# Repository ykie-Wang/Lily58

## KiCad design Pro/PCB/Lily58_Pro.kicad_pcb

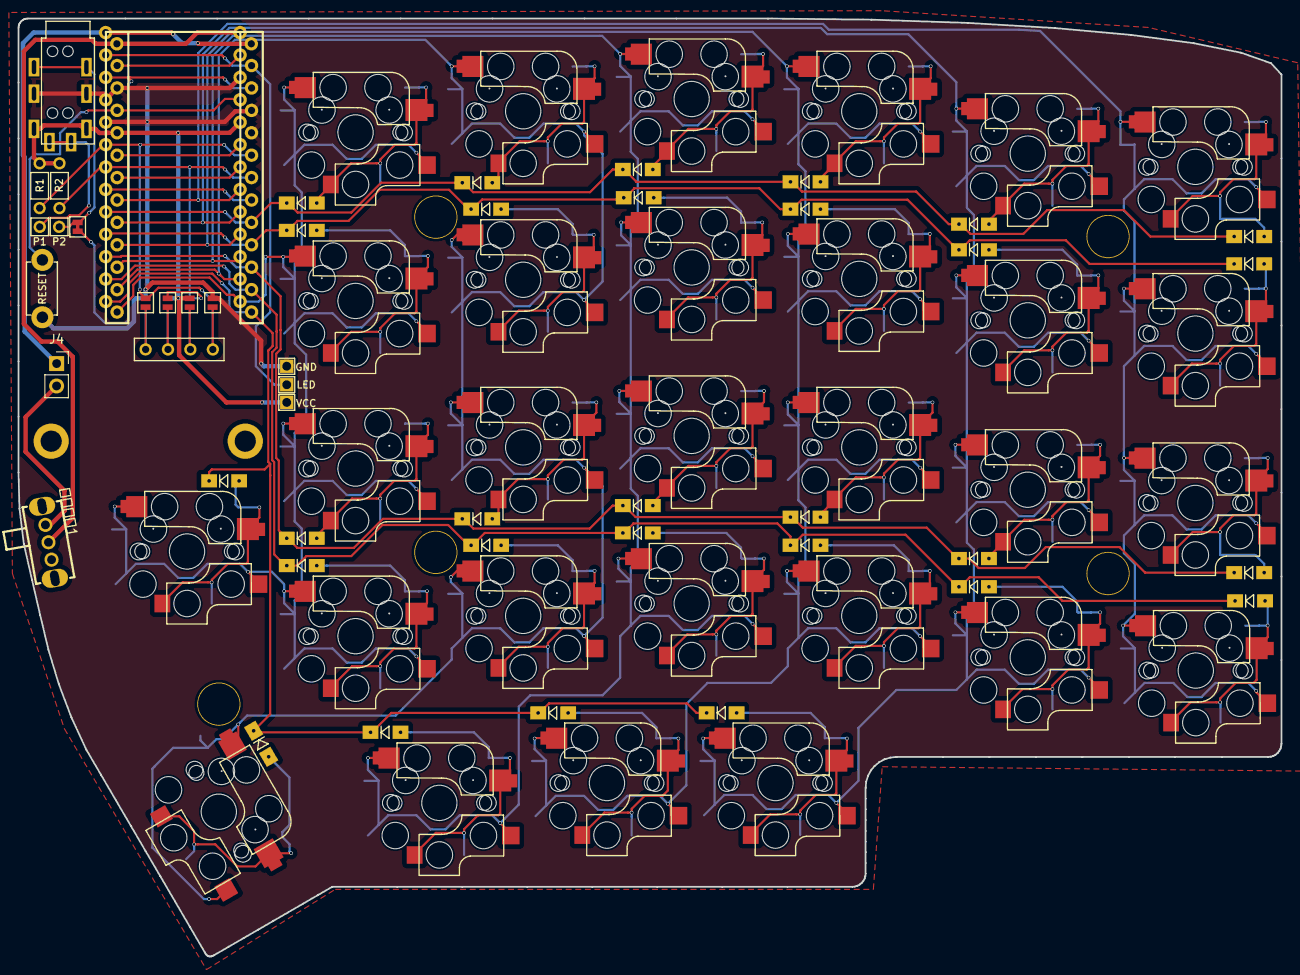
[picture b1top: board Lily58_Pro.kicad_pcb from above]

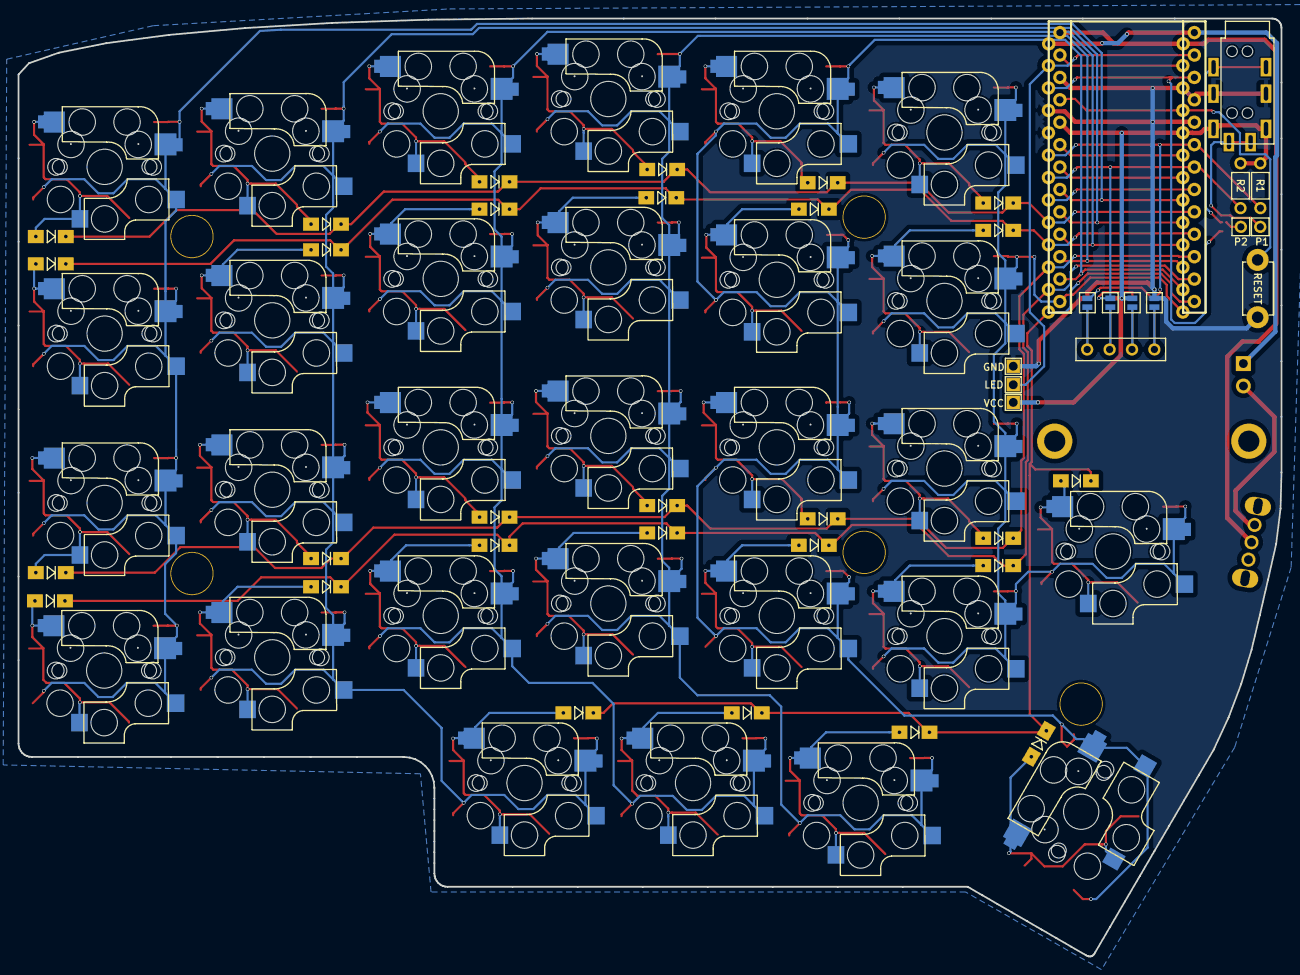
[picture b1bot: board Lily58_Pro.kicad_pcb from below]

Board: 2 copper layers, 143.2 x 106.3 mm, 85 parts (4 on the bottom side), 27 nets.

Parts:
D1, D2, D3, D4, D5, D6, D7, D8, D9, D10, D11, D12, D13, D14, D15, D16, D17, D18, D19, D20, D21, D22, D23, D24, D25, D26, D27, D28, D29: D; Diode_SOD123
J1: LED
J2: 4PIN; MJ-4PP-9
J3: OLED; OLED_4Pin
J4: Conn_01x02; PinSocket_1x02_P2.54mm_Vertical
JP1, JP2, JP3, JP4, JP5, JP6, JP7, JP8: Jumper_NO_Small; Jumper
P1, P2: i2c_pin; 1pin_conn
R1, R2: R; RESISTOR_mini
RSW1: SW_RST; TACT_SWITCH_TVBP06
SW1, SW2, SW3, SW4, SW5, SW6, SW7, SW8, SW9, SW10, SW11, SW12, SW13, SW14, SW15, SW16, SW17, SW18, SW19, SW20, SW21, SW22, SW23, SW24, SW25, SW26, SW27, SW28, SW29: SW_PUSH; CherryMX_KailhLowProfile_Hotswap_edge
TH1, TH2: HOLE; M2_HOLE_PCB
TH3, TH4, TH5, TH6, TH7: HOLE; HOLE_M2_TH
U1: nice_nano; NiceNano_rev2
W1: jumper; jumper_data
卧式开关1: SW-TH_SK12D07VG5

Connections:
Bnegative: J4.1, U1.1 (B-)
Bpositive: J4.2, 卧式开关1.1
DATA: U1.3 (RX1/P0.08), W1.1
GND: J1.3, J2.2, JP1.2, JP8.2, RSW1.1, U1.4 (GND), U1.5 (GND), U1.24 (GND)
LED: J1.2, U1.2 (TX0/P0.06)
unnamed: J3.1, JP4.1, JP8.1
unnamed: J3.2, JP3.1, JP7.1
unnamed: J3.3, JP2.1, JP6.1
unnamed: J3.4, JP1.1, JP5.1
unnamed: J2.4, P1.1
unnamed: J2.3, P2.1, W1.2
PowerIn: U1.26 (B+), 卧式开关1.2
RESET: RSW1.2, U1.23 (RST)
SCL: JP3.2, JP6.2, R2.2, U1.7 (P0.20)
SDA: JP4.2, JP5.2, R1.2, U1.6 (P0.17)
VCC: J1.1, J2.1, JP2.2, JP7.2, R1.1, R2.1, U1.22 (VCC)
col0: SW6.1, SW12.1, SW18.1, SW24.1, U1.19 (AIN0/P0.02)
col1: SW5.1, SW11.1, SW17.1, SW23.1, SW29.1, U1.18 (P1.15)
col2: SW4.1, SW10.1, SW16.1, SW22.1, SW28.1, U1.17 (P1.13)
col3: SW3.1, SW9.1, SW15.1, SW21.1, SW27.1, U1.16 (P1.11)
col4: SW2.1, SW8.1, SW14.1, SW20.1, SW26.1, U1.15 (NFC2/P0.10)
col5: SW1.1, SW7.1, SW13.1, SW19.1, SW25.1, U1.14 (NFC1/P0.09)
row0: D1.1 (K), D2.1 (K), D3.1 (K), D4.1 (K), D5.1 (K), D6.1 (K), U1.9 (P0.24)
row1: D7.1 (K), D8.1 (K), D9.1 (K), D10.1 (K), D11.1 (K), D12.1 (K), U1.10 (P1.00)
row2: D13.1 (K), D14.1 (K), D15.1 (K), D16.1 (K), D17.1 (K), D18.1 (K), U1.11 (P0.11)
row3: D19.1 (K), D20.1 (K), D21.1 (K), D22.1 (K), D23.1 (K), D24.1 (K), U1.12 (P1.04)
row4: D25.1 (K), D26.1 (K), D27.1 (K), D28.1 (K), D29.1 (K), U1.13 (P1.06)

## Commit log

2023-12-03 Wireless
